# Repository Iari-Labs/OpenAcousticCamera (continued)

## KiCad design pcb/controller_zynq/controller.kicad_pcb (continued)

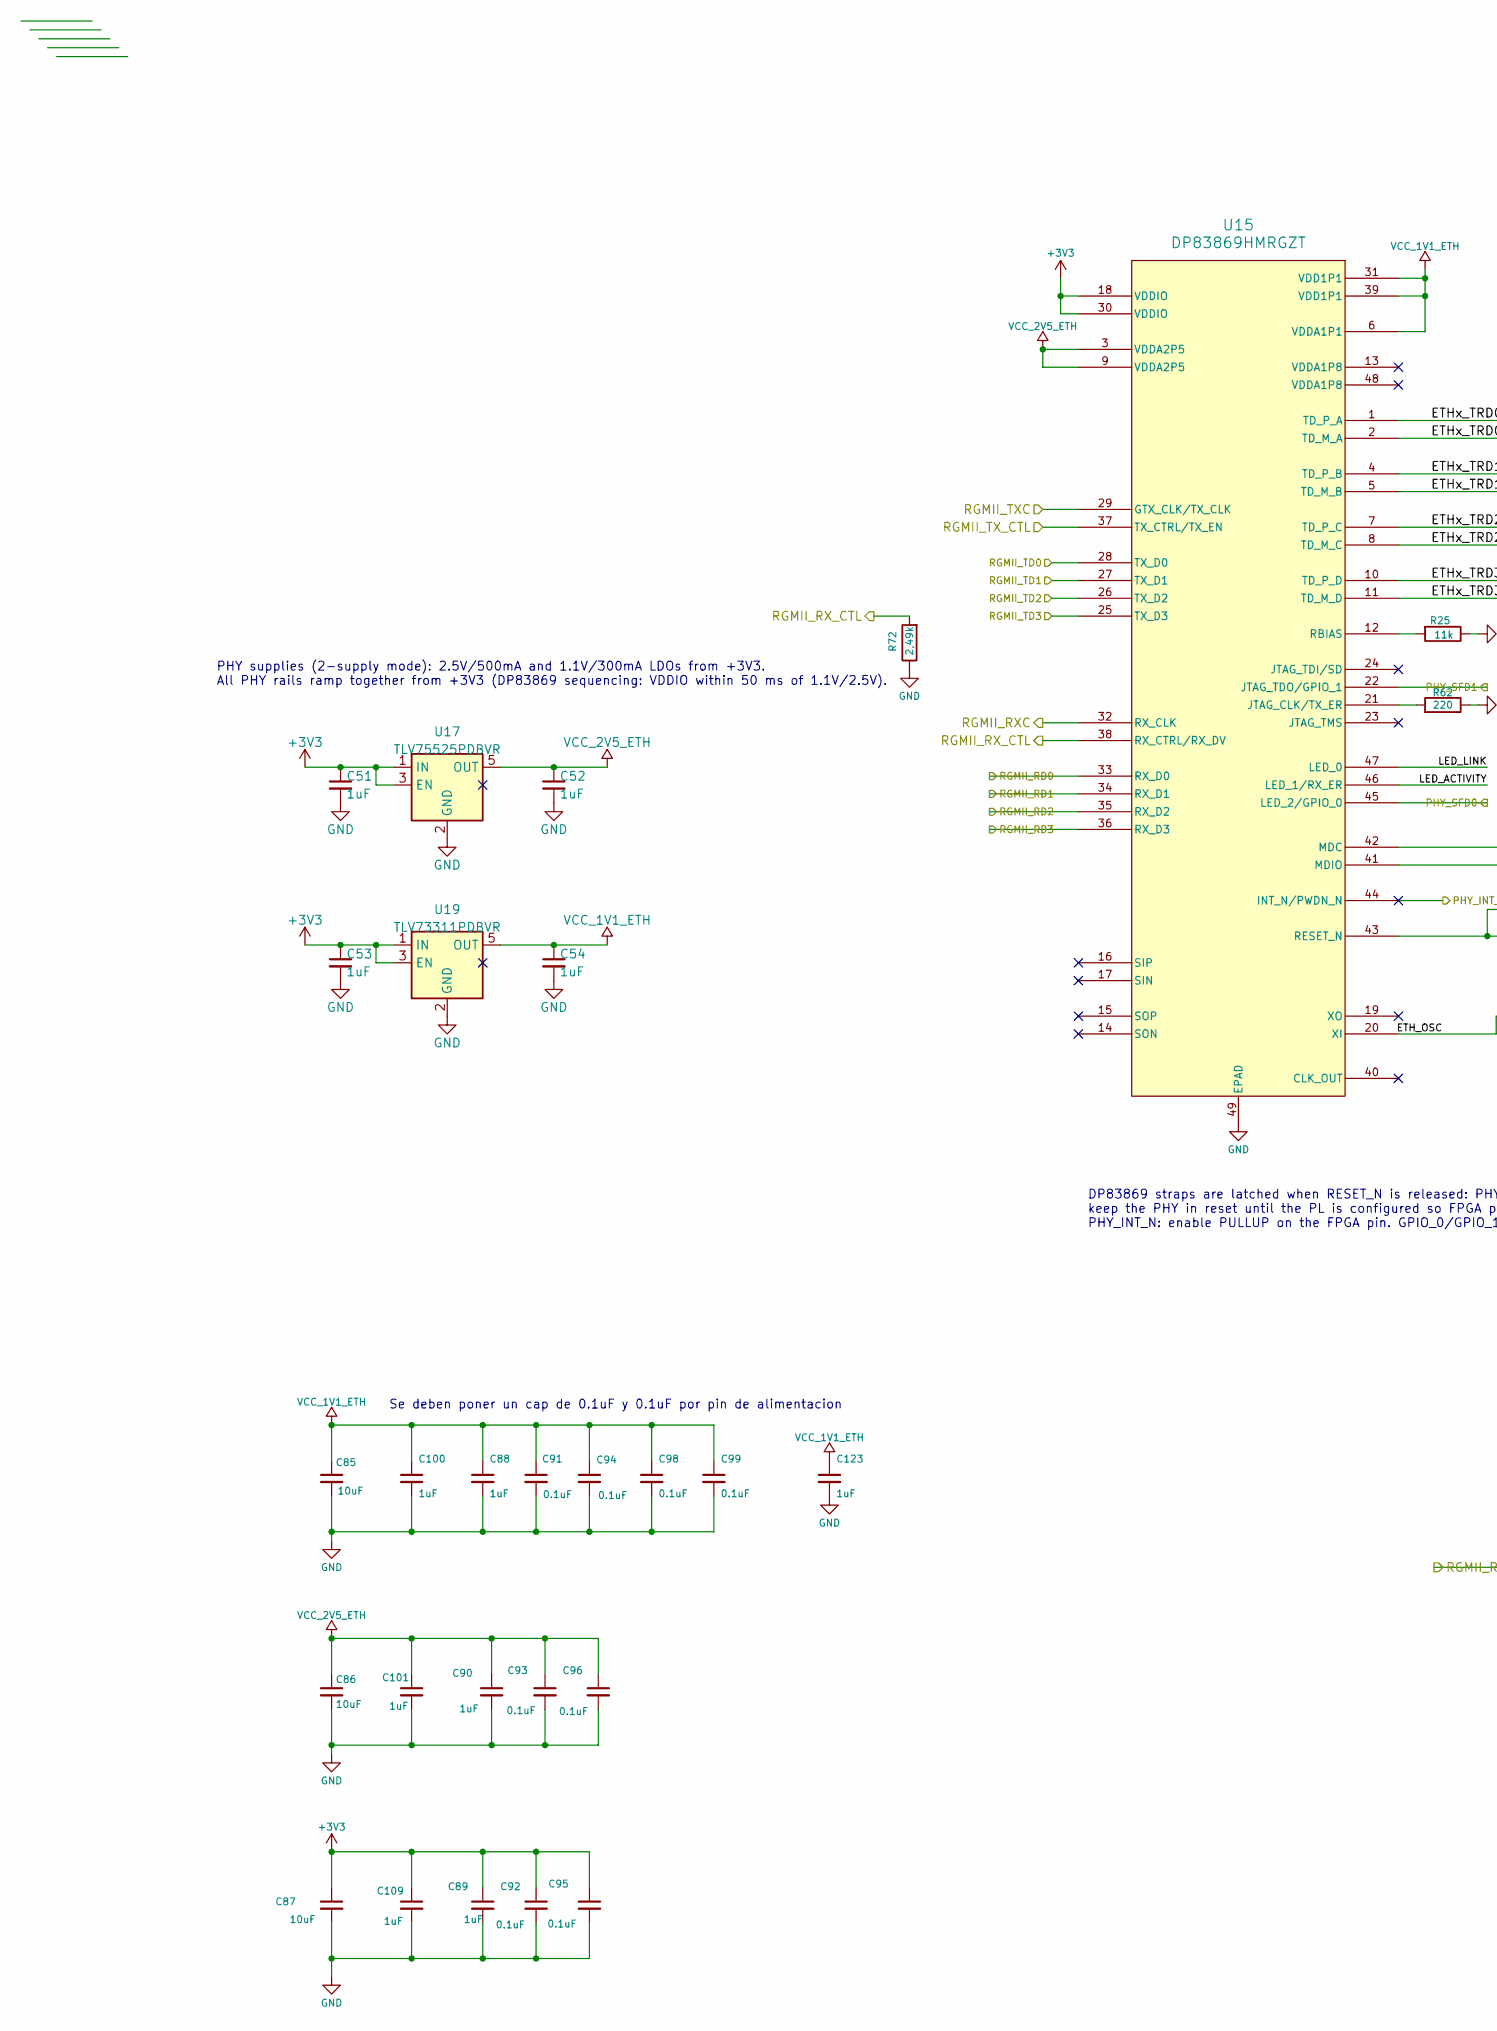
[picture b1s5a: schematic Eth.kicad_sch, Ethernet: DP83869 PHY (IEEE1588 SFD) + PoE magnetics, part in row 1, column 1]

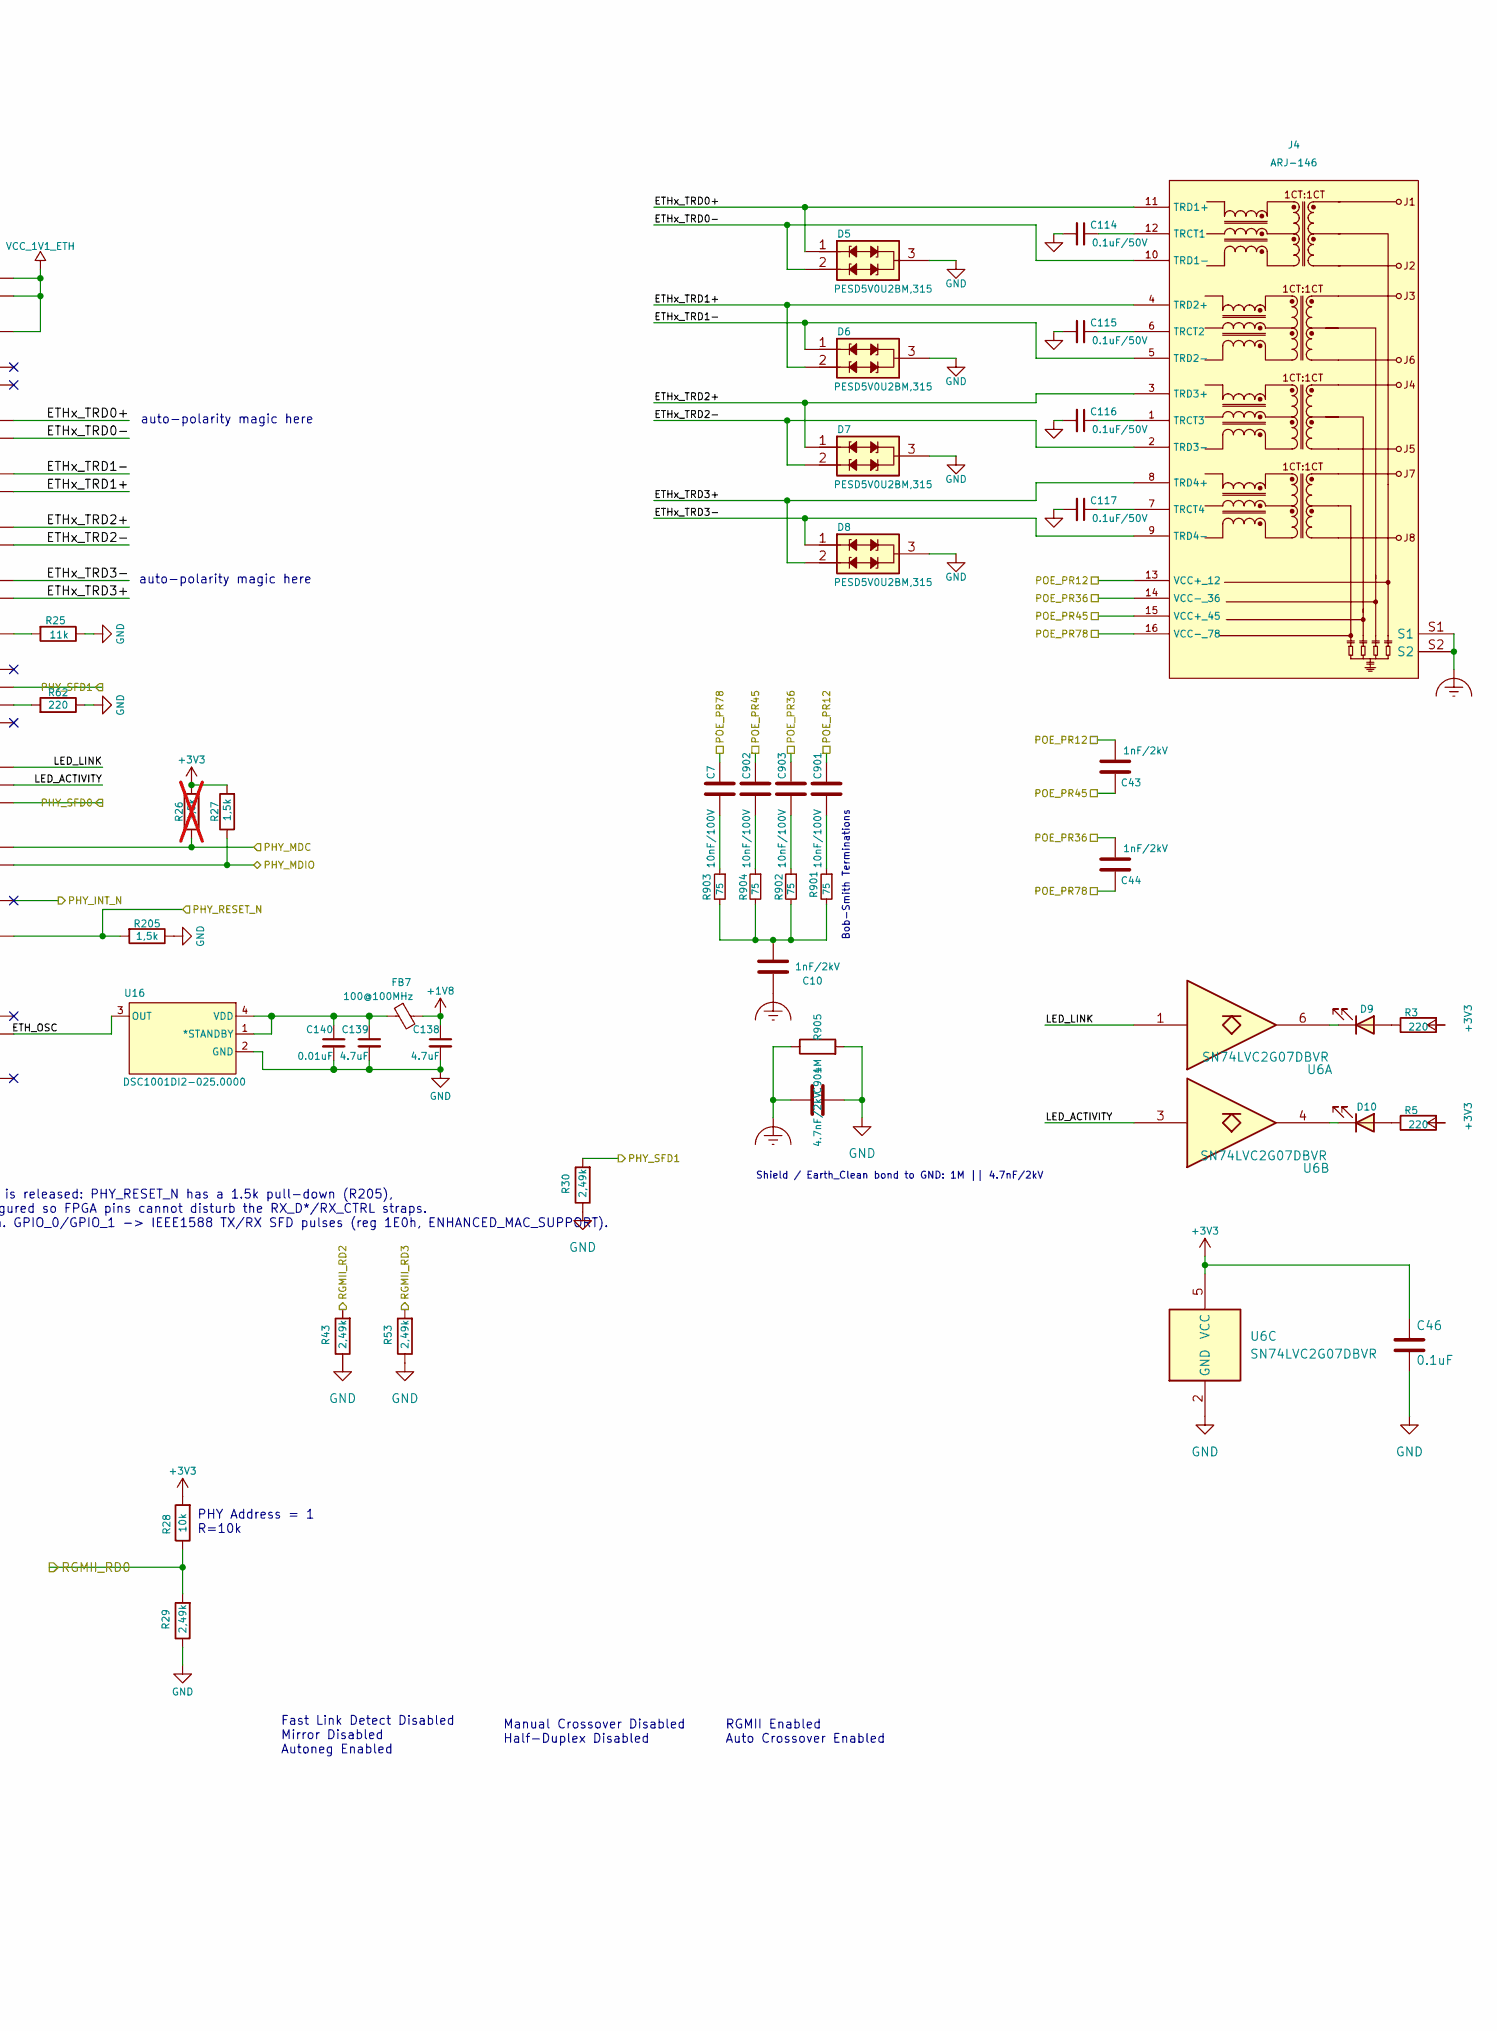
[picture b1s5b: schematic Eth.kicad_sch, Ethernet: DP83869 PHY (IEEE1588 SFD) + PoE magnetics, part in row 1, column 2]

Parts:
C7, C901, C902, C903: 10nF/100V; C_0805_2012Metric; Manufacturer_Part_Number CC0805KRX7R0BB103; LCSC C107135
C10, C43, C44: 1nF/2kV; C_1206_3216Metric; Manufacturer_Part_Number 1206B102K202NT; LCSC C9196
C46, C91, C92, C93, C94, C95, C96, C98, C99: 0.1uF; C_0201_0603Metric; Manufacturer_Part_Number GRM033R61E104KE14D; LCSC C76939
C51, C52, C53, C54: 1uF; C_0402_1005Metric
C85, C86, C87: 10uF; C_0603_1608Metric; Manufacturer_Part_Number GRM188R61C106KAALD; LCSC C86275
C88, C89, C90, C100, C101, C109, C123: 1uF; C_0402_1005Metric; Manufacturer_Part_Number CL05A105KA5NQNC; LCSC C52923
C114, C115, C116, C117: 0.1uF/50V; C_0402_1005Metric; Manufacturer_Part_Number GRM155R71H104KE14D; LCSC C77020
C138, C139: 4.7uF; C_0402_1005Metric; Manufacturer_Part_Number EDK105BBJ475MVLF; LCSC C412302
C140: 0.01uF; C_0201_0603Metric; Manufacturer_Part_Number GRM033R61E103KA12D; LCSC C76938
C904: 4.7nF/2kV; C_1812_4532Metric; Manufacturer_Part_Number GR442QR73D472KW01L
D5, D6, D7, D8: PESD5V0U2BM,315; PESD3V3L2UM315; Manufacturer_Part_Number PESD5V0U2BM,315; LCSC C552578
D9, D10: LED; APGA1602QBCKA5MAV; Manufacturer_Part_Number APGA1602CGC/KA; LCSC C5879397
FB7: 100@100MHz; L_0402_1005Metric; Manufacturer_Part_Number HCB1005KF-101T10; LCSC C356953
J4: ARJ-146; ARJ146; Manufacturer_Part_Number ARJ-146; LCSC C6465659
R3, R5, R62: 220; R_0201_0603Metric; Manufacturer_Part_Number RC0201FR-07220RL; LCSC C274342
R25: 11k; R_0201_0603Metric; Manufacturer_Part_Number RC0201FR-0711KL; LCSC C273275
R26: 1,5k; R_0201_0603Metric; Manufacturer_Part_Number RC0201FR-071K5L; LCSC C155737; not fitted
R27, R205: 1,5k; R_0201_0603Metric; Manufacturer_Part_Number RC0201FR-071K5L; LCSC C155737
R28: 10k; R_0201_0603Metric; Manufacturer_Part_Number RE0201BRE0710KL; LCSC C1882653
R29, R30, R43, R53, R72: 2,49k; R_0201_0603Metric; Manufacturer_Part_Number RC0201FR-072K49L; LCSC C273272
R901, R902, R903, R904: 75; R_0402_1005Metric; Manufacturer_Part_Number NQ02WGJ0750TCE; LCSC C25133
R905: 1M; R_1206_3216Metric; Manufacturer_Part_Number RC1206FR-071ML
U6: SN74LVC2G07DBVR; SOT-23-6; Manufacturer_Part_Number SN74LVC2G07DRYR; LCSC C7598673
U15: DP83869HMRGZT; RGZ0048B; Manufacturer_Part_Number DP83869HMRGZR; LCSC C2672408
U16: DSC1001DI2-025.0000; DSC1001DL2; Manufacturer_Part_Number DSC1001DI2-025.0000; LCSC C1670866
U17: TLV75525PDBVR; SOT-23-5; Manufacturer_Part_Number TLV75525PDBVR
U19: TLV73311PDBVR; SOT-23-5; Manufacturer_Part_Number TLV73311PDBVR

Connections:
+1V8: C138.1, FB7.2; also elsewhere on the board
+3V3: C46.1, C51.1, C53.1, C87.1, C89.1, C92.1, C95.1, C109.1, R3.2, R5.2, R26.2, R27.2, R28.2, U6.5 (VCC), U15.18 (VDDIO), U15.30 (VDDIO), U17.1 (IN), U17.3 (EN), U19.1 (IN), U19.3 (EN); also elsewhere on the board
/Ethernet/ETH_OSC: U15.20 (XI), U16.3 (OUT)
/Ethernet/ETHx_TRD0+: D5.1, J4.11 (TRD1+), U15.1 (TD_P_A)
/Ethernet/ETHx_TRD0-: D5.2, J4.10 (TRD1-), U15.2 (TD_M_A)
/Ethernet/ETHx_TRD1+: D6.2, J4.4 (TRD2+), U15.5 (TD_M_B)
/Ethernet/ETHx_TRD1-: D6.1, J4.5 (TRD2-), U15.4 (TD_P_B)
/Ethernet/ETHx_TRD2+: D7.1, J4.3 (TRD3+), U15.7 (TD_P_C)
/Ethernet/ETHx_TRD2-: D7.2, J4.2 (TRD3-), U15.8 (TD_M_C)
/Ethernet/ETHx_TRD3+: D8.2, J4.8 (TRD4+), U15.11 (TD_M_D)
/Ethernet/ETHx_TRD3-: D8.1, J4.9 (TRD4-), U15.10 (TD_P_D)
/Ethernet/LED_ACTIVITY: U6.3, U15.46 (LED_1/RX_ER)
/Ethernet/LED_LINK: U6.1, U15.47 (LED_0)
/Ethernet/PHY_INT_N: U15.44 (INT_N/PWDN_N); also elsewhere on the board
/Ethernet/PHY_MDC: R26.1, U15.42 (MDC); also elsewhere on the board
/Ethernet/PHY_MDIO: R27.1, U15.41 (MDIO); also elsewhere on the board
/Ethernet/PHY_RESET_N: R205.2, U15.43 (RESET_N); also elsewhere on the board
/Ethernet/PHY_SFD0: U15.45 (LED_2/GPIO_0); also elsewhere on the board
/Ethernet/PHY_SFD1: R30.2, U15.22 (JTAG_TDO/GPIO_1); also elsewhere on the board
/Ethernet/POE_PR12: C43.2, C901.1, J4.13 (VCC+_12); also elsewhere on the board
/Ethernet/POE_PR36: C44.2, C903.1, J4.14 (VCC-_36); also elsewhere on the board
/Ethernet/POE_PR45: C43.1, C902.1, J4.15 (VCC+_45); also elsewhere on the board
/Ethernet/POE_PR78: C7.1, C44.1, J4.16 (VCC-_78); also elsewhere on the board
/Ethernet/RGMII_RD0: R28.1, R29.2, U15.33 (RX_D0); also elsewhere on the board
/Ethernet/RGMII_RD1: U15.34 (RX_D1); also elsewhere on the board
/Ethernet/RGMII_RD2: R43.2, U15.35 (RX_D2); also elsewhere on the board
/Ethernet/RGMII_RD3: R53.2, U15.36 (RX_D3); also elsewhere on the board
/Ethernet/RGMII_RXC: U15.32 (RX_CLK); also elsewhere on the board
/Ethernet/RGMII_RX_CTL: R72.2, U15.38 (RX_CTRL/RX_DV); also elsewhere on the board
/Ethernet/RGMII_TD0: U15.28 (TX_D0); also elsewhere on the board
/Ethernet/RGMII_TD1: U15.27 (TX_D1); also elsewhere on the board
/Ethernet/RGMII_TD2: U15.26 (TX_D2); also elsewhere on the board
/Ethernet/RGMII_TD3: U15.25 (TX_D3); also elsewhere on the board
/Ethernet/RGMII_TXC: U15.29 (GTX_CLK/TX_CLK); also elsewhere on the board
/Ethernet/RGMII_TX_CTL: U15.37 (TX_CTRL/TX_EN); also elsewhere on the board
Earth_Clean: C10.2, C904.1, J4.S1, J4.S2, R905.1; also elsewhere on the board
GND: C46.2, C51.2, C52.2, C53.2, C54.2, C85.2, C86.2, C87.2, C88.2, C89.2, C90.2, C91.2, C92.2, C93.2, C94.2, C95.2, C96.2, C98.2, C99.2, C100.2, C101.2, C109.2, C114.2, C115.2, C116.2, C117.2, C123.2, C138.2, C139.2, C140.2, C904.2, D5.3, D6.3, D7.3, D8.3, R25.1, R29.1, R30.1, R43.1, R53.1, R62.1, R72.1, R205.1, R905.2, U6.2 (GND), U15.49 (EPAD), U16.2 (GND), U17.2 (GND), U19.2 (GND); also elsewhere on the board
unnamed: C7.2, R903.1
unnamed: C10.1, R901.2, R902.2, R903.2, R904.2
unnamed: C901.2, R901.1
unnamed: C902.2, R904.1
unnamed: C903.2, R902.1
unnamed: D9.2 (A), R3.1
unnamed: D9.1 (K), U6.6
unnamed: D10.2 (A), R5.1
unnamed: D10.1 (K), U6.4
unnamed: C114.1, J4.12 (TRCT1)
unnamed: C115.1, J4.6 (TRCT2)
unnamed: C116.1, J4.1 (TRCT3)
unnamed: C117.1, J4.7 (TRCT4)
unnamed: R62.2, U15.21 (JTAG_CLK/TX_ER)
unnamed: R25.2, U15.12 (RBIAS)
unnamed: C139.1, C140.1, FB7.1, U16.1 (*STANDBY), U16.4 (VDD)
VCC_1V1_ETH: C54.1, C85.1, C88.1, C91.1, C94.1, C98.1, C99.1, C100.1, C123.1, U15.6 (VDDA1P1), U15.31 (VDD1P1), U15.39 (VDD1P1), U19.5 (OUT)
VCC_2V5_ETH: C52.1, C86.1, C90.1, C93.1, C96.1, C101.1, U15.3 (VDDA2P5), U15.9 (VDDA2P5), U17.5 (OUT)

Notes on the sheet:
PHY supplies (2-supply mode): 2.5V/500mA and 1.1V/300mA LDOs from +3V3. All PHY rails ramp together from +3V3 (DP83869 sequencing: VDDIO within 50 ms of 1.1V/2.5V).
PHY Address = 1 R=10k
DP83869 straps are latched when RESET_N is released: PHY_RESET_N has a 1.5k pull-down (R205), keep the PHY in reset until the PL is configured so FPGA pins cannot disturb the RX_D*/RX_CTRL straps. PHY_INT_N: enable PULLUP on the FPGA pin. GPIO_0/GPIO_1 -> IEEE1588 TX/RX SFD pulses (reg 1E0h, ENHANC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
Manual Crossover Disabled Half-Duplex Disabled
auto-polarity magic here
Se deben poner un cap de 0.1uF y 0.1uF por pin de alimentacion
Bob-Smith Terminations
Shield / Earth_Clean bond to GND: 1M || 4.7nF/2kV
RGMII Enabled Auto Crossover Enabled
Fast Link Detect Disabled Mirror Disabled Autoneg Enabled

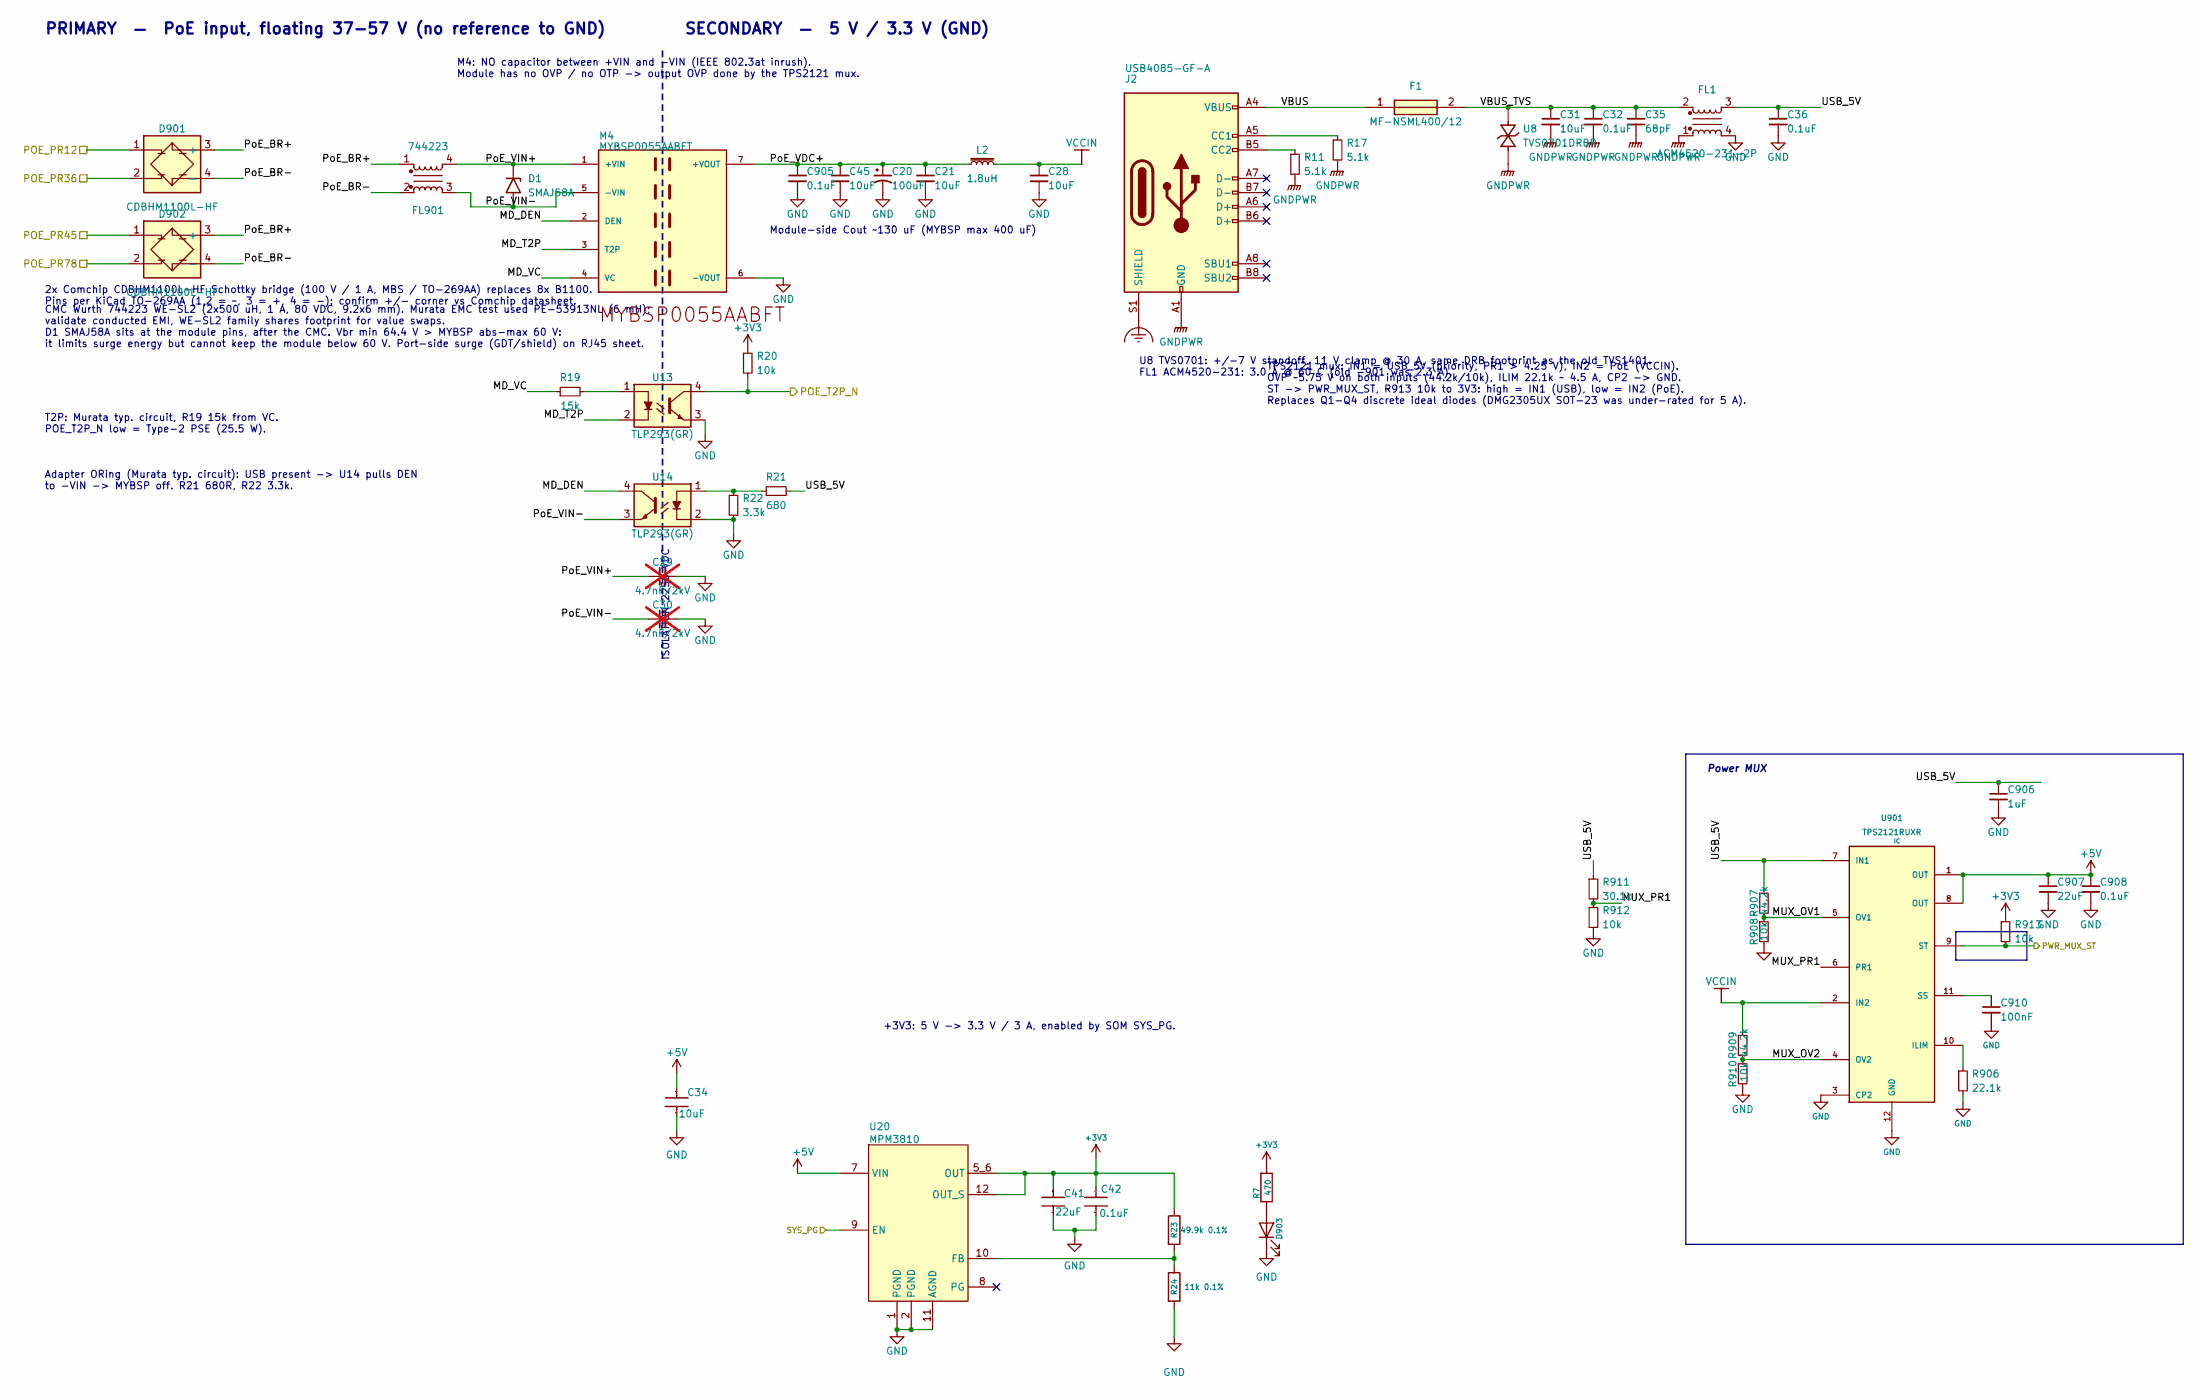
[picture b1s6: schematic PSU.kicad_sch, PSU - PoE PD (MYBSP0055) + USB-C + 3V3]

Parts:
C20: 100uF; CP_Elec_6.3x5.9; Manufacturer_Part_Number RVT1C101M0605; LCSC C37308
C21, C28, C31: 10uF; C_0603_1608Metric; Manufacturer_Part_Number CL10A106KP8NNNC; LCSC C19702
C29, C30: 4.7nF/2kV; C_1812_4532Metric; Manufacturer_Part_Number GR442QR73D472KW01L; not fitted
C32, C36: 0.1uF; C_0201_0603Metric; Manufacturer_Part_Number 0201X104K160NT; LCSC C2846674
C34: 10uF; C_0603_1608Metric; Manufacturer_Part_Number GRM188R61C106KAALD; LCSC C86275
C35: 68pF; C_0201_0603Metric; Manufacturer_Part_Number 0201CG680J250NT; LCSC C285057
C41: 22uF; C_0603_1608Metric; Manufacturer_Part_Number CL10A226MQ8NRNC; LCSC C59461
C42: 0.1uF; C_0201_0603Metric; Manufacturer_Part_Number GRM033R61E104KE14D; LCSC C76939
C45: 10uF; C_0805_2012Metric; Manufacturer_Part_Number CL21A106KAYNNNE; LCSC C15850
C905, C908: 0.1uF; C_0402_1005Metric; Manufacturer_Part_Number CL05B104KO5NNNC; LCSC C1525
C906: 1uF; C_0402_1005Metric; Manufacturer_Part_Number CL05A105KA5NQNC; LCSC C52923
C907: 22uF; C_1206_3216Metric; Manufacturer_Part_Number CL31A226KAHNNNE; LCSC C12891
C910: 100nF; C_0402_1005Metric; Manufacturer_Part_Number CL05B104KO5NNNC; LCSC C1525
D1: SMAJ58A; D_SMA; Manufacturer_Part_Number SMAJ58A; LCSC C10762
D901, D902: CDBHM1100L-HF; TO-269AA; Manufacturer_Part_Number CDBHM1100L-HF; LCSC C5179685
D903: LED; APGA1602QBCKA5MAV; Manufacturer_Part_Number APGA1602CGC/KA; LCSC C5879397
F1: MF-NSML400/12; FUSC3216X120N; Manufacturer_Part_Number MF-NSML400/12-2; LCSC C2760306
FL1: ACM4520-231-2P; ACM4520_TDK; Manufacturer_Part_Number ACM4520-231-2P-T000
FL901: 744223; WE-SL2; Manufacturer_Part_Number 744223
J2: USB4085-GF-A; USB_C_Receptacle_GCT_USB4085; Manufacturer_Part_Number USB4085-GF-A; LCSC C7095263
L2: 1.8uH; L_Changjiang_FNR4020S; Manufacturer_Part_Number 74438356018; LCSC C167824
M4: MYBSP0055AABFT; MURATA_MYBSP0055AABFT_0
R7: 470; R_0201_0603Metric; Manufacturer_Part_Number RC0201FR-07470RL; LCSC C295802
R11, R17: 5.1k; R_0201_0603Metric; Manufacturer_Part_Number ERJ-1GNJ512C; LCSC C270344
R19: 15k; R_0201_0603Metric; Manufacturer_Part_Number ERJ-1GNJ153C
R20: 10k; R_0201_0603Metric; Manufacturer_Part_Number ERJ-1GNF1002C; LCSC C166388
R21: 680; R_0603_1608Metric; Manufacturer_Part_Number ERJ-3EKF6800V
R22: 3.3k; R_0201_0603Metric; Manufacturer_Part_Number ERJ-1GNF3301C
R23: 49.9k 0.1%; R_0402_1005Metric; Manufacturer_Part_Number ERA-2AEB4992X; LCSC C2073457
R24: 11k 0.1%; R_0402_1005Metric; Manufacturer_Part_Number AC0402DR-0711KL; LCSC C226682
R906: 22.1k; R_0402_1005Metric; Manufacturer_Part_Number ERJ-2RKF2212X
R907, R909: 44.2k; R_0402_1005Metric; Manufacturer_Part_Number ERJ-2RKF4422X
R908, R910, R912, R913: 10k; R_0402_1005Metric; Manufacturer_Part_Number ERJ-2RKF1002X
R911: 30.1k; R_0402_1005Metric; Manufacturer_Part_Number ERJ-2RKF3012X
U8: TVS0701DRBR; VSON8_DRB_TEX; Manufacturer_Part_Number TVS0701DRBR
U13, U14: TLP293(GR); SOIC-4_4.55x2.6mm_P1.27mm; Manufacturer_Part_Number TLP293(GR-TPL,E
U20: MPM3810; CONV_MPM3810AGQB-AEC1-Z; Manufacturer_Part_Number MPM3810AGQB-AEC1-Z; LCSC C6228655
U901: TPS2121RUXR; IC_TPS2121RUXR

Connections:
+3V3: C41.1, C42.2, R7.2, R20.1, R23.1, R913.1, U20.5_6 (OUT), U20.12 (OUT_S); also elsewhere on the board
+5V: C34.1, C907.1, C908.1, U20.7 (VIN), U901.1 (OUT), U901.8 (OUT); also elsewhere on the board
/Ethernet/POE_PR12: D901.1; also elsewhere on the board
/Ethernet/POE_PR36: D901.2; also elsewhere on the board
/Ethernet/POE_PR45: D902.1; also elsewhere on the board
/Ethernet/POE_PR78: D902.2; also elsewhere on the board
/PSU/MD_DEN: M4.2 (DEN), U14.4 (C)
/PSU/MD_T2P: M4.3 (T2P), U13.2 (K)
/PSU/MD_VC: M4.4 (VC), R19.1
/PSU/MUX_OV1: R907.2, R908.1, U901.5 (OV1)
/PSU/MUX_OV2: R909.2, R910.1, U901.4 (OV2)
/PSU/MUX_PR1: R911.2, R912.1, U901.6 (PR1)
/PSU/POE_T2P_N: R20.2, U13.4 (C); also elsewhere on the board
/PSU/PWR_MUX_ST: R913.2, U901.9 (ST)
/PSU/PoE_BR+: D901.3 (+), D902.3 (+), FL901.1
/PSU/PoE_BR-: D901.4 (-), D902.4 (-), FL901.2
/PSU/PoE_VDC+: C20.1, C21.1, C45.1, C905.1, L2.1, M4.7 (+VOUT)
/PSU/PoE_VIN+: C29.1, D1.1 (A1), FL901.4, M4.1 (+VIN)
/PSU/PoE_VIN-: C30.1, D1.2 (A2), FL901.3, M4.5 (-VIN), U14.3 (E)
/PSU/SYS_PG: U20.9 (EN); also elsewhere on the board
/PSU/USB_5V: C36.1, C906.1, FL1.3, R21.2, R907.1, R911.1, U901.7 (IN1)
/PSU/VBUS: F1.1, J2.A4 (VBUS), J2.A9 (VBUS), J2.B4 (VBUS), J2.B9 (VBUS)
/PSU/VBUS_TVS: C31.1, C32.1, C35.1, F1.2, FL1.2, U8.1 (IN), U8.2 (IN), U8.3 (IN), U8.4 (IN)
Earth_Clean: J2.S1 (SHIELD); also elsewhere on the board
GND: C20.2, C21.2, C28.2, C29.2, C30.2, C34.2, C36.2, C41.2, C42.1, C45.2, C905.2, C906.2, C907.2, C908.2, C910.2, D903.1 (K), FL1.4, M4.6 (-VOUT), R22.2, R24.2, R906.2, R908.2, R910.2, R912.2, U13.3 (E), U14.2 (K), U20.1 (PGND), U20.2 (PGND), U20.11 (AGND), U901.3 (CP2), U901.12 (GND); also elsewhere on the board
GNDPWR: C31.2, C32.2, C35.2, FL1.1, J2.A1 (GND), J2.A12 (GND), J2.B1 (GND), J2.B12 (GND), R11.2, R17.2, U8.5 (GND), U8.6 (GND), U8.7 (GND), U8.8 (GND)
unnamed: D903.2 (A), R7.1
unnamed: J2.A5 (CC1), R17.1
unnamed: J2.B5 (CC2), R11.1
unnamed: R19.2, U13.1 (A)
unnamed: R21.1, R22.1, U14.1 (A)
unnamed: R23.2, R24.1, U20.10 (FB)
unnamed: R906.1, U901.10 (ILIM)
unnamed: C910.1, U901.11 (SS)
VCCIN: C28.1, L2.2, R909.1, U901.2 (IN2)

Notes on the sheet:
Module-side Cout ~130 uF (MYBSP max 400 uF)
SECONDARY — 5 V / 3.3 V (GND)
T2P: Murata typ. circuit, R19 15k from VC. POE_T2P_N low = Type-2 PSE (25.5 W).
ISOLATION 2250 VDC
PRIMARY — PoE input, floating 37-57 V (no reference to GND)
Power MUX
2x Comchip CDBHM1100L-HF Schottky bridge (100 V / 1 A, MBS / TO-269AA) replaces 8x B1100. Pins per KiCad TO-269AA (1,2 = ~, 3 = +, 4 = -): confirm +/- corner vs Comchip datasheet.
CMC Wurth 744223 WE-SL2 (2x500 uH, 1 A, 80 VDC, 9.2x6 mm). Murata EMC test used PE-53913NL (6 mH); validate conducted EMI, WE-SL2 family shares footprint for value swaps. D1 SMAJ58A sits at the module pins, after the CMC. Vbr min 64.4 V > MYBSP abs-max 60 V: it limits surge energy but cannot keep t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
U8 TVS0701: +/-7 V standoff, 11 V clamp @ 30 A, same DRB footprint as the old TVS1401. FL1 ACM4520-231: 3.0 A @ 60 C (old -901 was 2.3 A).
+3V3: 5 V -> 3.3 V / 3 A, enabled by SOM SYS_PG.
M4: NO capacitor between +VIN and -VIN (IEEE 802.3at inrush). Module has no OVP / no OTP -> output OVP done by the TPS2121 mux.
Adapter ORing (Murata typ. circuit): USB present -> U14 pulls DEN to -VIN -> MYBSP off. R21 680R, R22 3.3k.
TPS2121 mux: IN1 = USB_5V (priority, PR1 > 4.25 V), IN2 = PoE (VCCIN). OVP ~5.75 V on both inputs (44.2k/10k), ILIM 22.1k ~ 4.5 A, CP2 -> GND. ST -> PWR_MUX_ST, R913 10k to 3V3: high = IN1 (USB), low = IN2 (PoE). Replaces Q1-Q4 discrete ideal diodes (DMG2305UX SOT-23 was under-rated for 5 A).

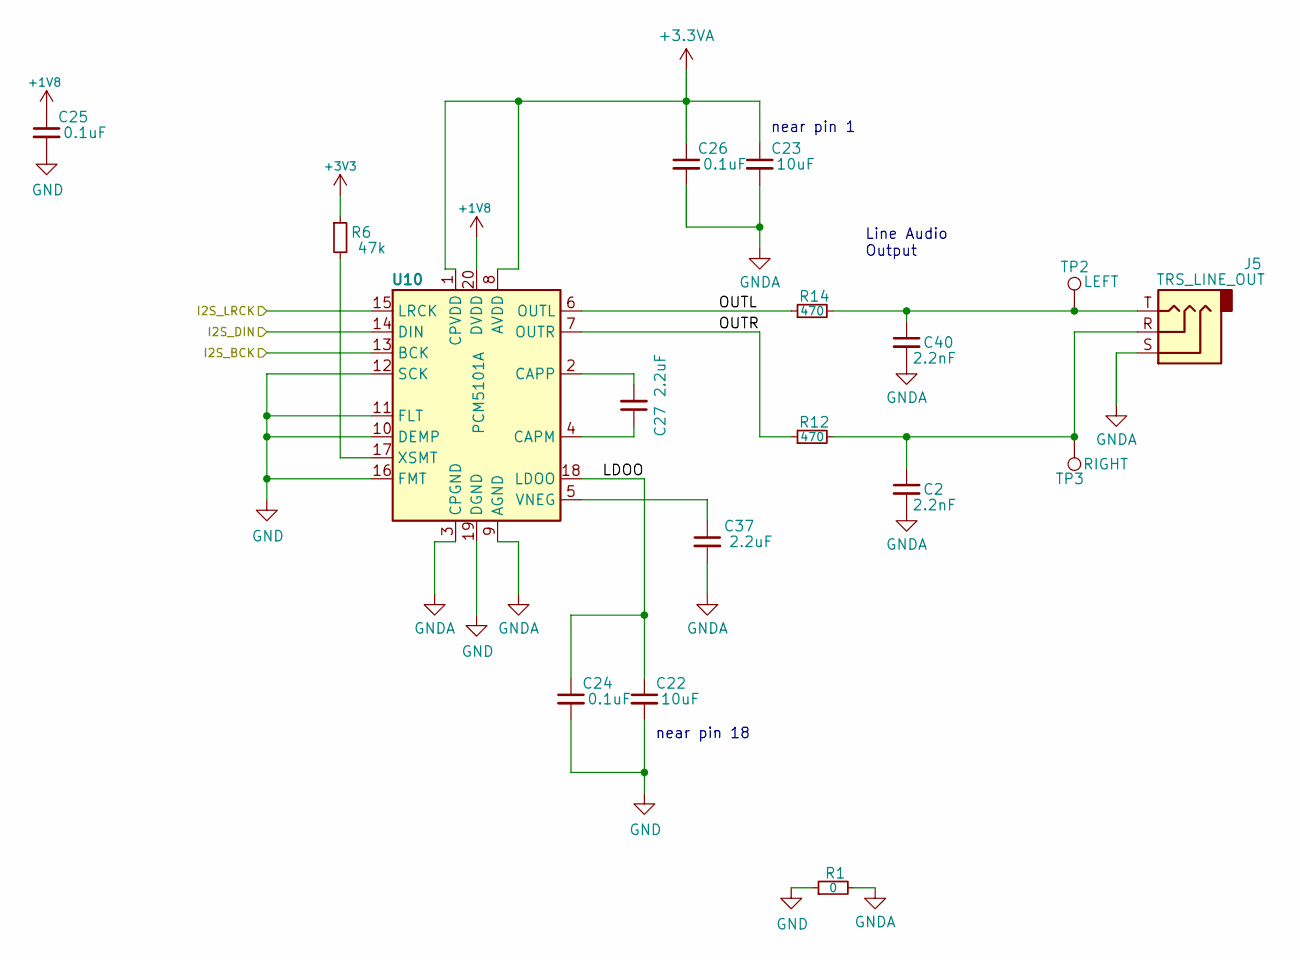
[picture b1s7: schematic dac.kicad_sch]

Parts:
C2, C40: 2.2nF; C_0603_1608Metric; Manufacturer_Part_Number CL10C222JB8NNNC; LCSC C33353
C22, C23: 10uF; C_0603_1608Metric; Manufacturer_Part_Number CL10A106KP8NNNC; LCSC C19702
C24, C25, C26: 0.1uF; C_0201_0603Metric; Manufacturer_Part_Number 0201X104K160NT; LCSC C2846674
C27, C37: 2.2uF; C_0603_1608Metric; Manufacturer_Part_Number CL10A225KO8NNNC; LCSC C23630
J5: TRS_LINE_OUT; C18594; Manufacturer_Part_Number PJ-320B; LCSC C18594
R1: 0; R_0603_1608Metric; LCSC C21189
R6: 47k; R_0201_0603Metric; Manufacturer_Part_Number 1GNF4702C; LCSC C270345
R12, R14: 470; R_0402_1005Metric; Manufacturer_Part_Number 0402WGF470LTCE; LCSC C423162
TP2: LEFT; TestPoint_Pad_D1.0mm
TP3: RIGHT; TestPoint_Pad_D1.0mm
U10: PCM5101A; TSSOP-20_4.4x6.5mm_P0.65mm; Manufacturer_Part_Number PCM5101APW; LCSC C1540128

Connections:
+1V8: C25.1, U10.20 (DVDD); also elsewhere on the board
+3.3VA: C23.1, C26.1, U10.1 (CPVDD), U10.8 (AVDD)
+3V3: R6.1; also elsewhere on the board
/DAC/I2S_BCK: U10.13 (BCK); also elsewhere on the board
/DAC/I2S_DIN: U10.14 (DIN); also elsewhere on the board
/DAC/I2S_LRCK: U10.15 (LRCK); also elsewhere on the board
/DAC/LDOO: C22.1, C24.1, U10.18 (LDOO)
/DAC/OUTL: R14.1, U10.6 (OUTL)
/DAC/OUTR: R12.1, U10.7 (OUTR)
GND: C22.2, C24.2, C25.2, R1.1, U10.10 (DEMP), U10.11 (FLT), U10.12 (SCK), U10.16 (FMT), U10.19 (DGND); also elsewhere on the board
GNDA: C2.2, C23.2, C26.2, C37.2, C40.2, J5.S, R1.2, U10.3 (CPGND), U10.9 (AGND)
unnamed: C2.1, J5.R, R12.2, TP3.1 (1_1)
unnamed: C40.1, J5.T, R14.2, TP2.1 (1_1)
unnamed: C27.1, U10.4 (CAPM)
unnamed: C27.2, U10.2 (CAPP)
unnamed: C37.1, U10.5 (VNEG)
unnamed: R6.2, U10.17 (XSMT)

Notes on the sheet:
near pin 18
near pin 1
Line Audio Output

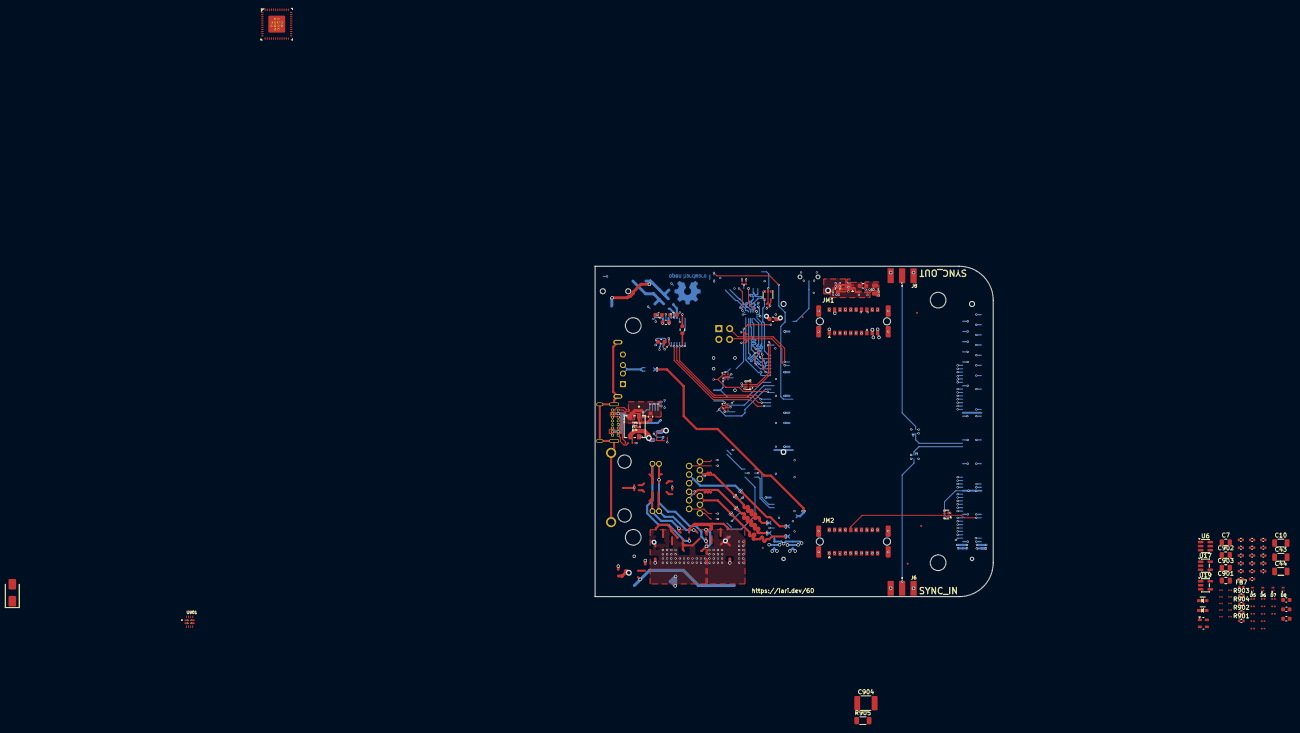
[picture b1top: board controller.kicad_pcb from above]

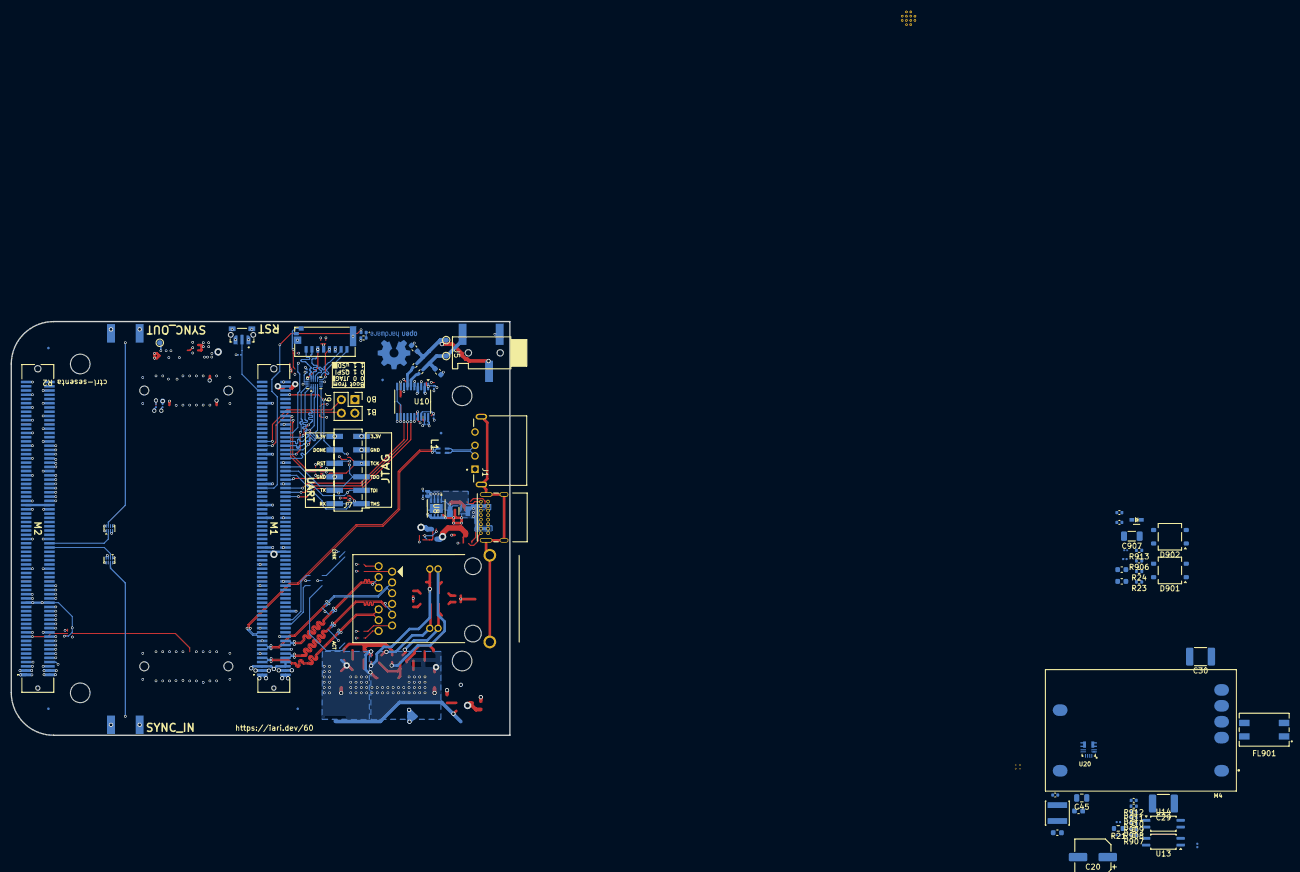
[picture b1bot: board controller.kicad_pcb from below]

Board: 6 copper layers, 94.0 x 78.0 mm, 192 parts (79 on the bottom side), 174 nets.
